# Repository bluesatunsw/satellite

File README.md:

# Satellite
Bluesat's CubeSat project.

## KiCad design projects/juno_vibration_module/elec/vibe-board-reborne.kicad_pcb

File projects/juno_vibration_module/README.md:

## Bluesat Juno Vibration Module

The current directory contains the code for the UNSW Rocketry vibration module. The components used for this project are:
- A NUCLEO F042K6
- A microSD card connected via SPI
- An IMU module connected via I2C

Documentation is located at:
<https://bluesat.atlassian.net/wiki/spaces/SP/pages/3017867282/Vibration+Module>

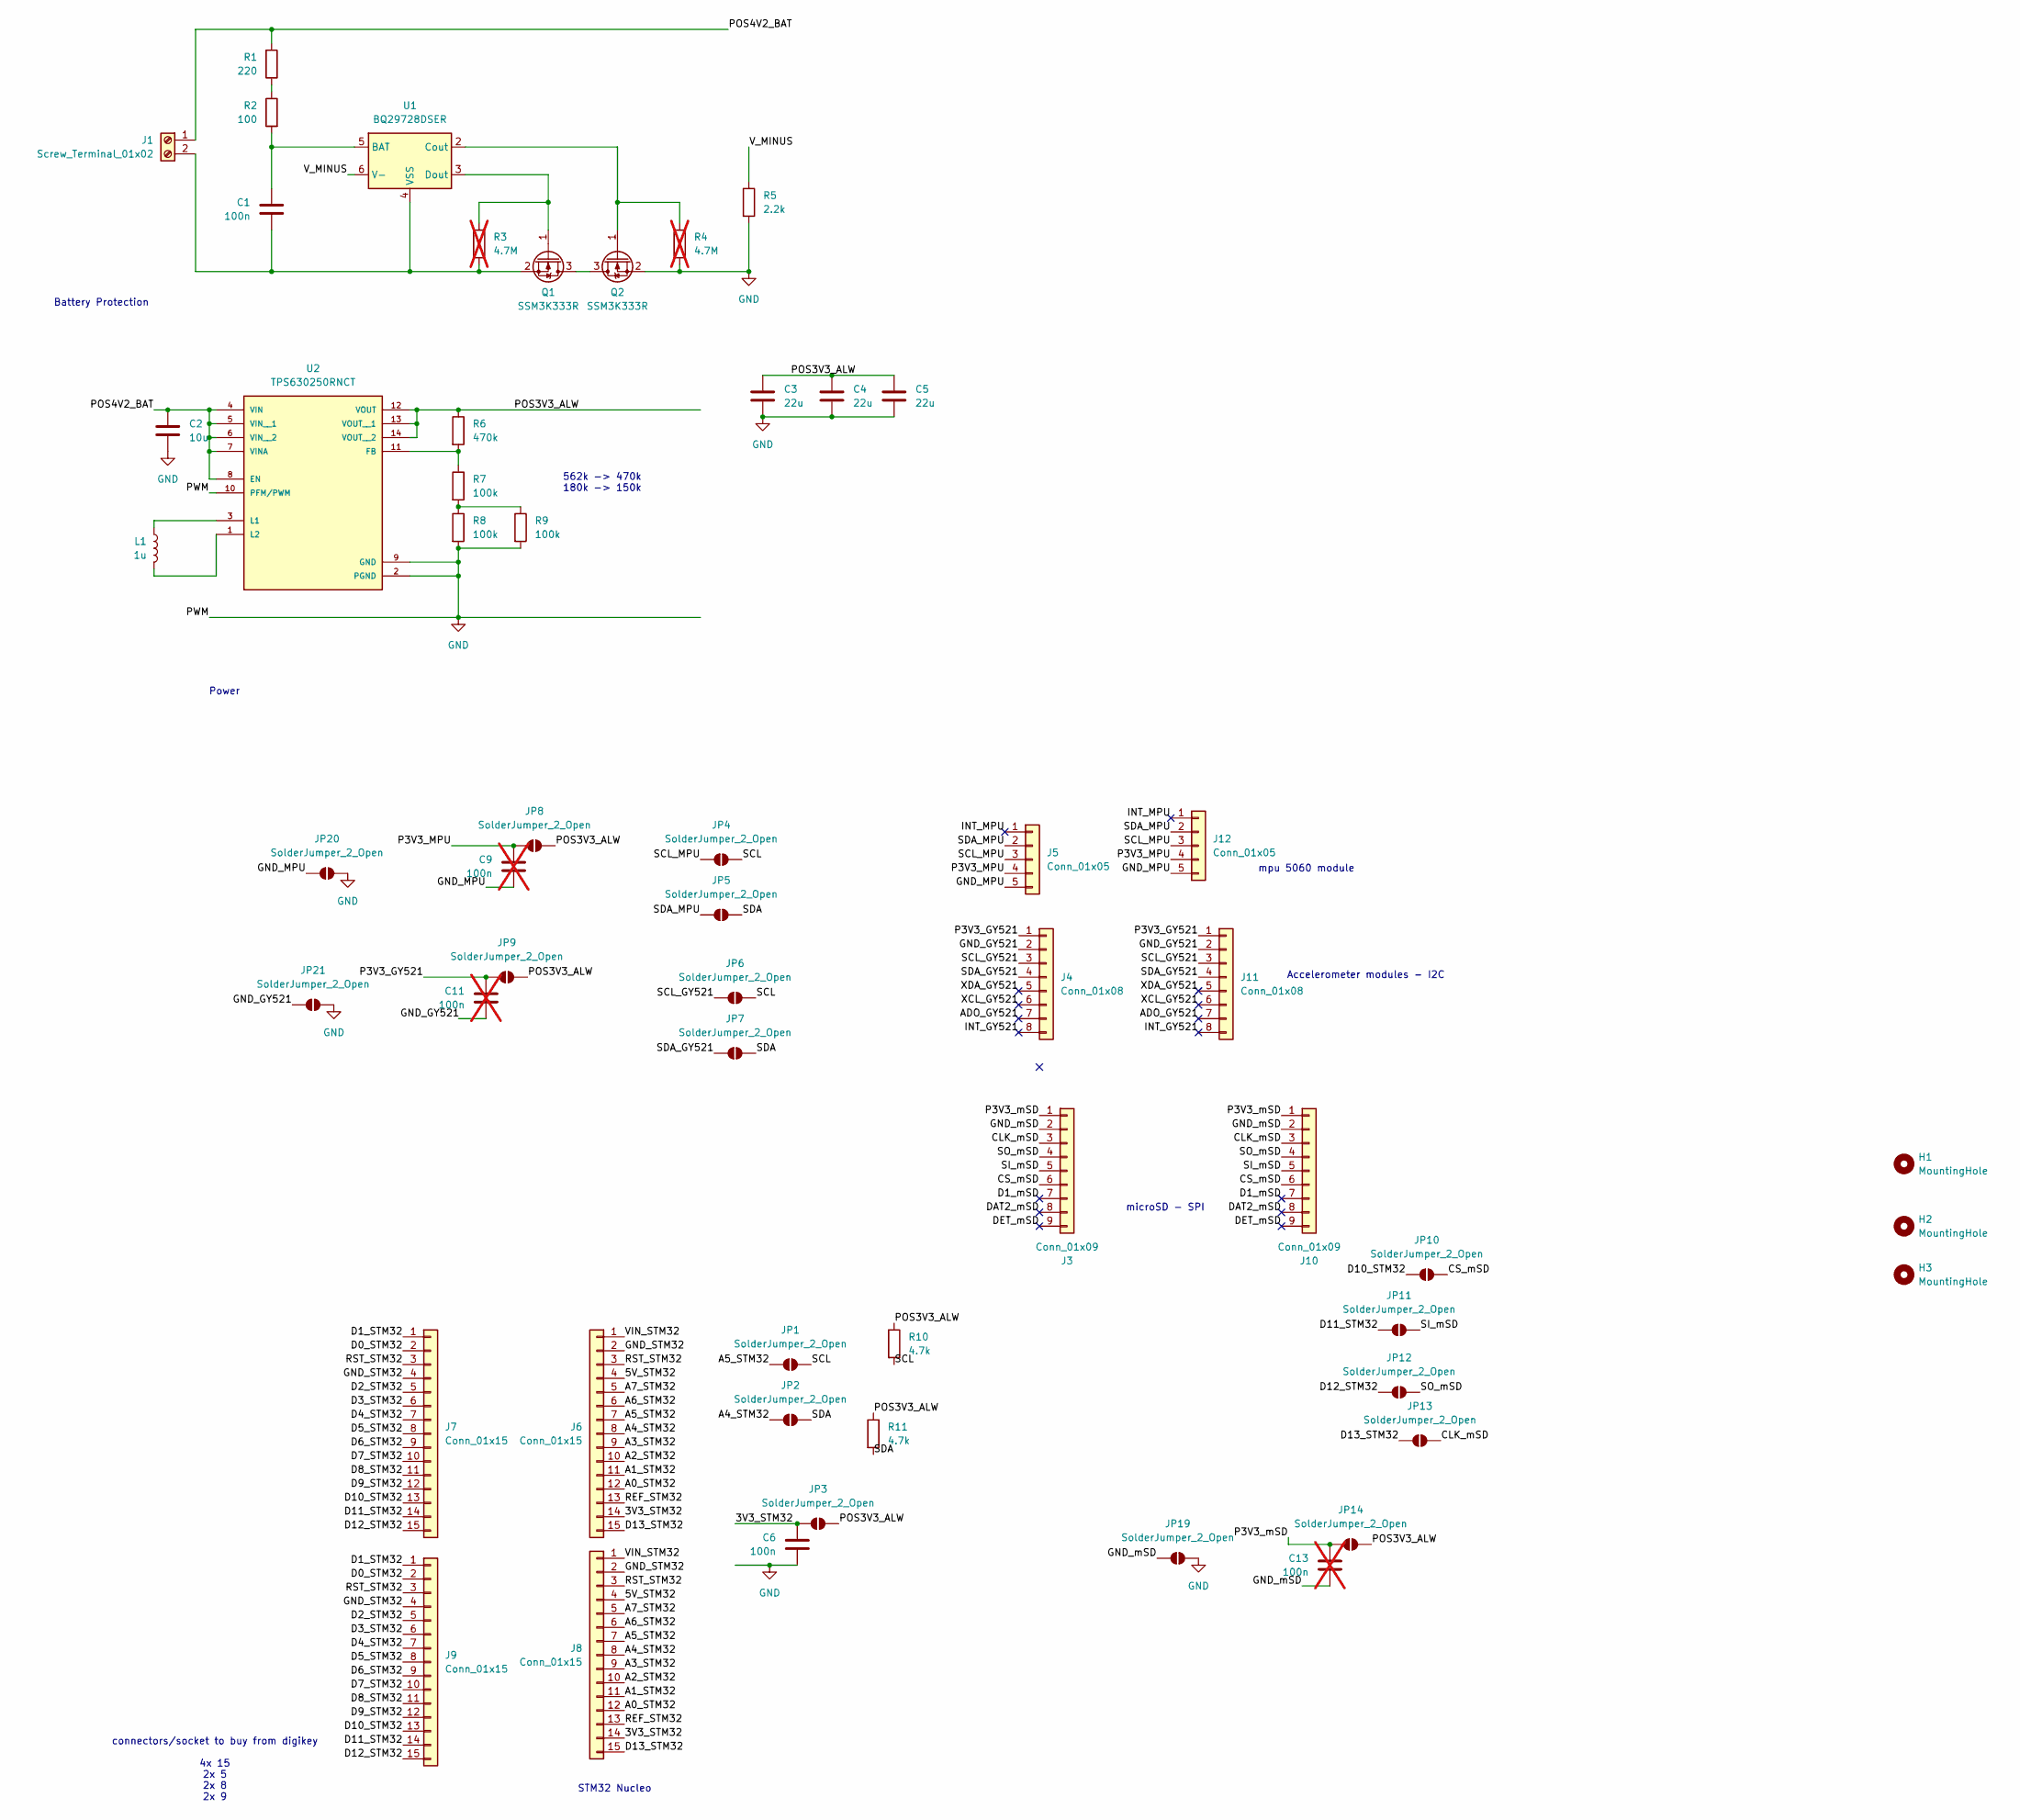
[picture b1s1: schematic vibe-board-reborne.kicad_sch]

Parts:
C1, C6: 100n; C_0402_1005Metric_Pad0.74x0.62mm_HandSolder
C2: 10u; C_1210_3225Metric
C3, C4, C5: 22u; C_1210_3225Metric
C9, C11, C13: 100n; C_0402_1005Metric_Pad0.74x0.62mm_HandSolder; not fitted
H1, H2, H3: MountingHole; MountingHole_3.2mm_M3
J1: Screw_Terminal_01x02; 34_102
J3, J10: Conn_01x09; PinSocket_1x09_P2.54mm_Vertical
J4, J11: Conn_01x08; PinSocket_1x08_P2.54mm_Vertical
J5, J12: Conn_01x05; PinSocket_1x05_P2.54mm_Vertical
J6, J7, J8, J9: Conn_01x15; PinSocket_1x15_P2.54mm_Vertical
JP1, JP2, JP3, JP4, JP5, JP6, JP7, JP8, JP9, JP10, JP11, JP12, JP13, JP14, JP19, JP20, JP21: SolderJumper_2_Open; SolderJumper-2_P1.3mm_Open_RoundedPad1.0x1.5mm
L1: 1u; L_Changjiang_FXL0630
Q1, Q2: SSM3K333R; SOT-23_Handsoldering
R1: 220; R_0402_1005Metric_Pad0.72x0.64mm_HandSolder
R2: 100; R_0402_1005Metric_Pad0.72x0.64mm_HandSolder
R3, R4: 4.7M; R_0402_1005Metric_Pad0.72x0.64mm_HandSolder; not fitted
R5: 2.2k; R_0402_1005Metric_Pad0.72x0.64mm_HandSolder
R6: 470k; R_0402_1005Metric_Pad0.72x0.64mm_HandSolder
R7, R8, R9: 100k; R_0402_1005Metric_Pad0.72x0.64mm_HandSolder
R10, R11: 4.7k; R_0402_1005Metric_Pad0.72x0.64mm_HandSolder
U1: BQ29728DSER; WSON-6_1.5x1.5mm_P0.5mm
U2: TPS630250RNCT; PARTREV B

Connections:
/3V3_STM32: C6.1, J6.14, J8.14, JP3.1 (A)
/5V_STM32: J6.4, J8.4
/A0_STM32: J6.12, J8.12
/A1_STM32: J6.11, J8.11
/A2_STM32: J6.10, J8.10
/A3_STM32: J6.9, J8.9
/A4_STM32: J6.8, J8.8, JP2.1 (A)
/A5_STM32: J6.7, J8.7, JP1.1 (A)
/A6_STM32: J6.6, J8.6
/A7_STM32: J6.5, J8.5
/ADO_GY521: J4.7, J11.7
/CLK_mSD: J3.3, J10.3, JP13.2 (B)
/CS_mSD: J3.6, J10.6, JP10.2 (B)
/D0_STM32: J7.2, J9.2
/D1_STM32: J7.1, J9.1
/D1_mSD: J3.7, J10.7
/D2_STM32: J7.5, J9.5
/D3_STM32: J7.6, J9.6
/D4_STM32: J7.7, J9.7
/D5_STM32: J7.8, J9.8
/D6_STM32: J7.9, J9.9
/D7_STM32: J7.10, J9.10
/D8_STM32: J7.11, J9.11
/D9_STM32: J7.12, J9.12
/D10_STM32: J7.13, J9.13, JP10.1 (A)
/D11_STM32: J7.14, J9.14, JP11.1 (A)
/D12_STM32: J7.15, J9.15, JP12.1 (A)
/D13_STM32: J6.15, J8.15, JP13.1 (A)
/DAT2_mSD: J3.8, J10.8
/DET_mSD: J3.9, J10.9
/GND_GY521: C11.2, J4.2, J11.2, JP21.1 (A)
/GND_MPU: C9.2, J5.5, J12.5, JP20.1 (A)
/GND_STM32: J6.2, J7.4, J8.2, J9.4
/GND_mSD: C13.2, J3.2, J10.2, JP19.1 (A)
/INT_GY521: J4.8, J11.8
/INT_MPU: J5.1, J12.1
/P3V3_GY521: C11.1, J4.1, J11.1, JP9.1 (A)
/P3V3_MPU: C9.1, J5.4, J12.4, JP8.1 (A)
/P3V3_mSD: C13.1, J3.1, J10.1, JP14.1 (A)
/POS3V3_ALW: C3.1, C4.1, C5.1, JP3.2 (B), JP8.2 (B), JP9.2 (B), JP14.2 (B), R6.1, R10.1, R11.1, U2.12 (VOUT), U2.13 (VOUT__1), U2.14 (VOUT__2)
/POS4V2_BAT: C2.1, J1.1, R1.2, U2.4 (VIN), U2.5 (VIN__1), U2.6 (VIN__2), U2.7 (VINA), U2.8 (EN)
/REF_STM32: J6.13, J8.13
/RST_STM32: J6.3, J7.3, J8.3, J9.3
/SCL: JP1.2 (B), JP4.2 (B), JP6.2 (B), R10.2
/SCL_GY521: J4.3, J11.3, JP6.1 (A)
/SCL_MPU: J5.3, J12.3, JP4.1 (A)
/SDA: JP2.2 (B), JP5.2 (B), JP7.2 (B), R11.2
/SDA_GY521: J4.4, J11.4, JP7.1 (A)
/SDA_MPU: J5.2, J12.2, JP5.1 (A)
/SI_mSD: J3.5, J10.5, JP11.2 (B)
/SO_mSD: J3.4, J10.4, JP12.2 (B)
/VIN_STM32: J6.1, J8.1
/V_MINUS: R5.1, U1.6 (V-)
/XCL_GY521: J4.6, J11.6
/XDA_GY521: J4.5, J11.5
GND: C2.2, C3.2, C4.2, C5.2, C6.2, JP19.2 (B), JP20.2 (B), JP21.2 (B), Q2.2 (S), R4.2, R5.2, R8.2, R9.2, U2.2 (PGND), U2.9 (GND), U2.10 (PFM/PWM)
unnamed: C1.2, J1.2, Q1.2 (S), R3.2, U1.4 (VSS)
unnamed: Q1.3 (D), Q2.3 (D)
unnamed: Q1.1 (G), R3.1, U1.3 (Dout)
unnamed: Q2.1 (G), R4.1, U1.2 (Cout)
unnamed: R1.1, R2.1
unnamed: R7.2, R8.1, R9.1
unnamed: C1.1, R2.2, U1.5 (BAT)
unnamed: R6.2, R7.1, U2.11 (FB)
unnamed: L1.1, U2.3 (L1)
unnamed: L1.2, U2.1 (L2)

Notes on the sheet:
Accelerometer modules - I2C
mpu 5060 module
connectors/socket to buy from digikey 4x 15 2x 5 2x 8 2x 9
Power
Battery Protection
562k -> 470k 180k -> 150k
microSD - SPI
STM32 Nucleo

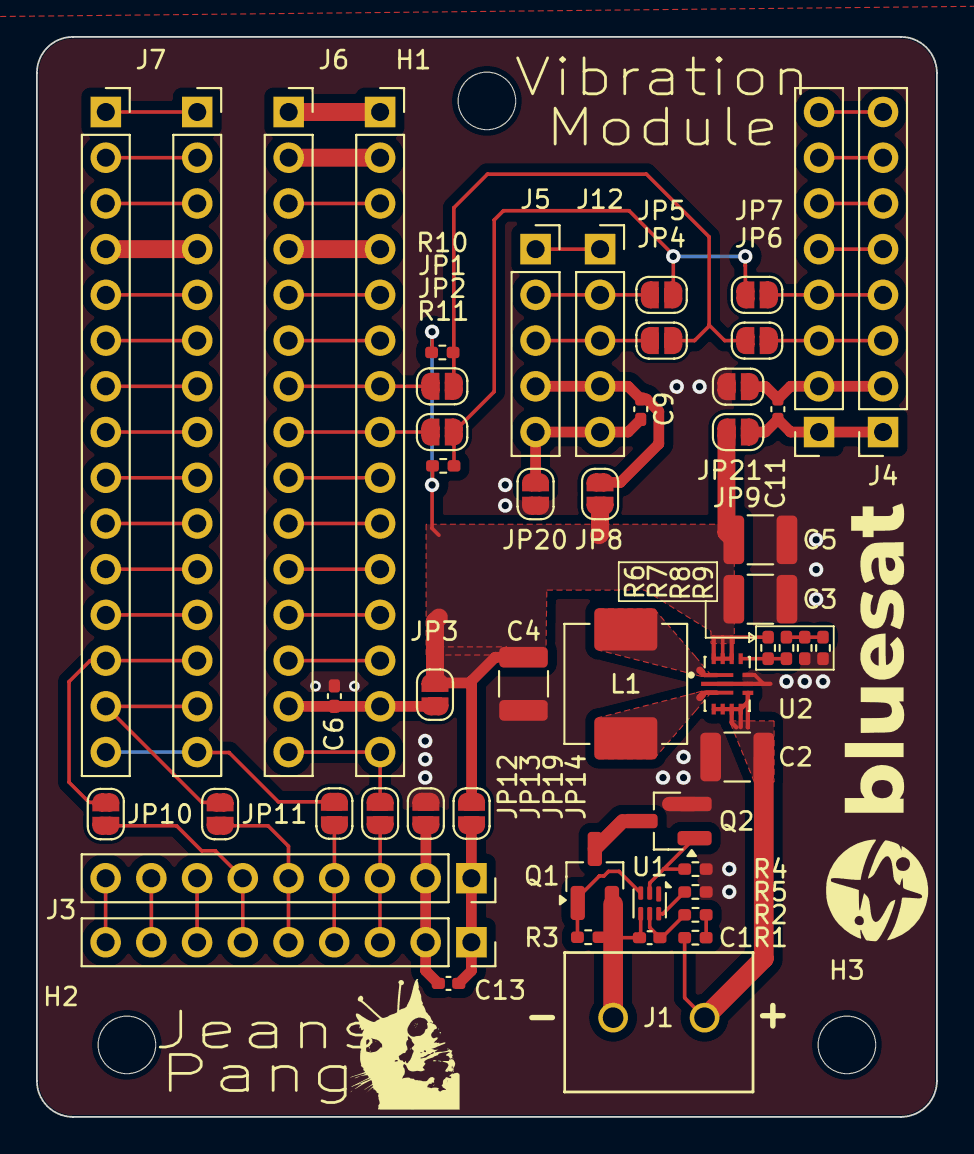
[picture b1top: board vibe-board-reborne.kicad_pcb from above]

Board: 2 copper layers, 50.0 x 60.0 mm, 56 parts (0 on the bottom side), 66 nets.

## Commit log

2026-03-09 feat: upload vibration module code
2026-03-14 added elec files
2026-03-15 Added /elec and system block diagram
2026-03-26 chore: refactor juno vibration module
2026-03-26 chore(placeholder): init a software folder
2026-04-16 Initial commit of BMS
2026-04-17 Move BMS Kicad files into elec folder
2026-04-17 Move BMS kicad files into power directory
2026-04-17 Add power budget
2026-04-17 Just another commit
2026-04-23 Sensor data logging psuedo code
2026-05-15 BMS schematic almost done + components are assigned their footpritns except connectors
2026-05-15 LED Driver schematic version 1
    Version 1, as of 15 May 2026
2026-05-15 Pretty much what I can do until this point
2026-05-18 Add fuel gauge schematic
2026-05-19 Added UV LCD board (Kratika) doler
2026-05-19 Moved UV LCD board files
2026-05-19 Renamed the very first LED Driver folder with the old schematic to OLD LED driver
2026-05-19 Add files via upload
    New LED driver schematic with the UV LED custom footprint
2026-05-19 rename
2026-05-19 deleted random md file
2026-05-19 added .gitignore (thx owr)
2026-05-19 apply gitignore and removed kicad backups etc
2026-05-19 Adding OBC board V0.1 KiCad files
2026-05-19 applying modified owr gitignore and remove ignored files
2026-05-19 added OWR library as of 19 May 2026
2026-05-19 added OWR common library as of 19 May 2026
2026-05-20 tidying up UV LCD schematic and adding motor driver schematic
2026-05-20 moved old project files to sandbox
2026-05-20 Post PDR State and upgraded to KiCad v10
2026-05-21 Added LED driver symbol, UV LED symbol and UV LED footprint to uv_lcd folder using gitbash
2026-05-21 Updated the spacing between pad and silkscreen on LED footprint
